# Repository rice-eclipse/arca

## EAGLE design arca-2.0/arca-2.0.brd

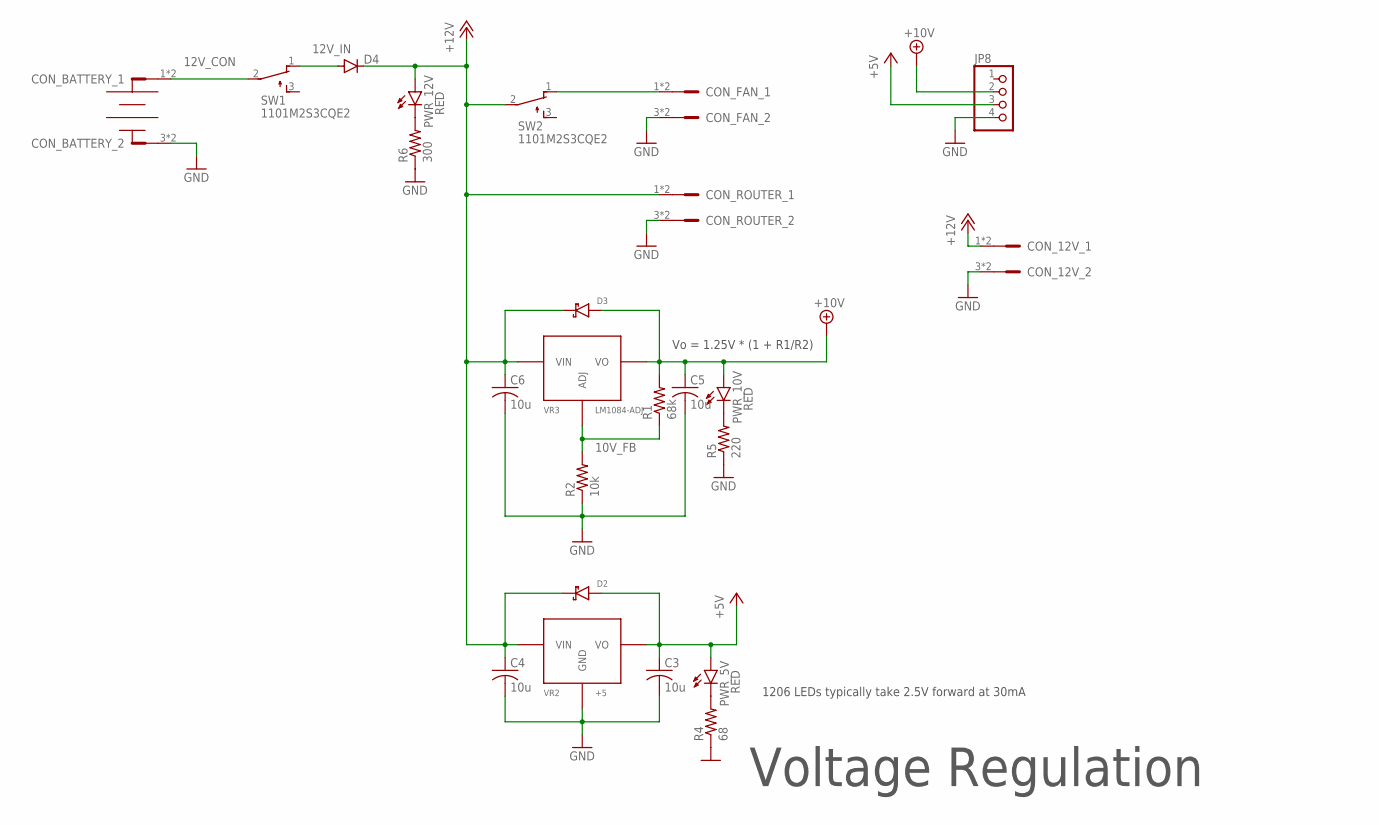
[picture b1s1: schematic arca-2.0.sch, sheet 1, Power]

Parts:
C3, C4, C5, C6: 10u; C1206
CON_12V: LPTA-2POS; 8.2X2
CON_BATTERY: LPTA-2POS; 8.2X2
CON_FAN: LPTA-2POS; 8.2X2
CON_ROUTER: LPTA-2POS; 8.2X2
D2, D3: SS54; SS*
D4: DIODE-DO201-15; DO201-15
JP8: PINHD-1X4; 1X04
PWR_5V, PWR_10V, PWR_12V: RED; CHIPLED_1206
R1: 68k; R1206
R2: 10k; R1206
R4: 68; R1206
R5: 220; R1206
R6: 300; R1206
SW1, SW2: 1101M2S3CQE2
VR2: +5; TO-263-3L
VR3: LM1084-ADJ; TO-263-3L

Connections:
10V_FB: R1.1, R2.2, VR3.P$1 (ADJ)
12V_CON: CON_BATTERY.1, CON_BATTERY.2, SW1.2
12V_IN: D4.A, SW1.1 (O)
+5V: C3.1, D2.P$2, JP8.3, PWR_5V.A, VR2.P$2 (VO), VR2.P$4 (VO), VR2.P$5 (VO); also elsewhere on the board
+10V: C5.1, D3.P$2, JP8.2, PWR_10V.A, R1.2, VR3.P$2 (VO), VR3.P$4 (VO), VR3.P$5 (VO); also elsewhere on the board
+12V: C4.1, C6.1, CON_12V.1, CON_12V.2, CON_ROUTER.1, CON_ROUTER.2, D2.P$1, D3.P$1, D4.C, PWR_12V.A, SW2.2, VR2.P$3 (VIN), VR3.P$3 (VIN); also elsewhere on the board
GND: C3.2, C4.2, C5.2, C6.2, CON_12V.3, CON_12V.4, CON_BATTERY.3, CON_BATTERY.4, CON_FAN.3, CON_FAN.4, CON_ROUTER.3, CON_ROUTER.4, JP8.4, R2.1, R4.1, R5.1, R6.1, VR2.P$1 (GND); also elsewhere on the board
unnamed: PWR_5V.C, R4.2
unnamed: PWR_10V.C, R5.2
unnamed: PWR_12V.C, R6.2
unnamed: CON_FAN.1, CON_FAN.2, SW2.1 (O)

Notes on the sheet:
Vo = 1.25V * (1 + R1/R2)
1206 LEDs typically take 2.5V forward at 30mA
Voltage Regulation

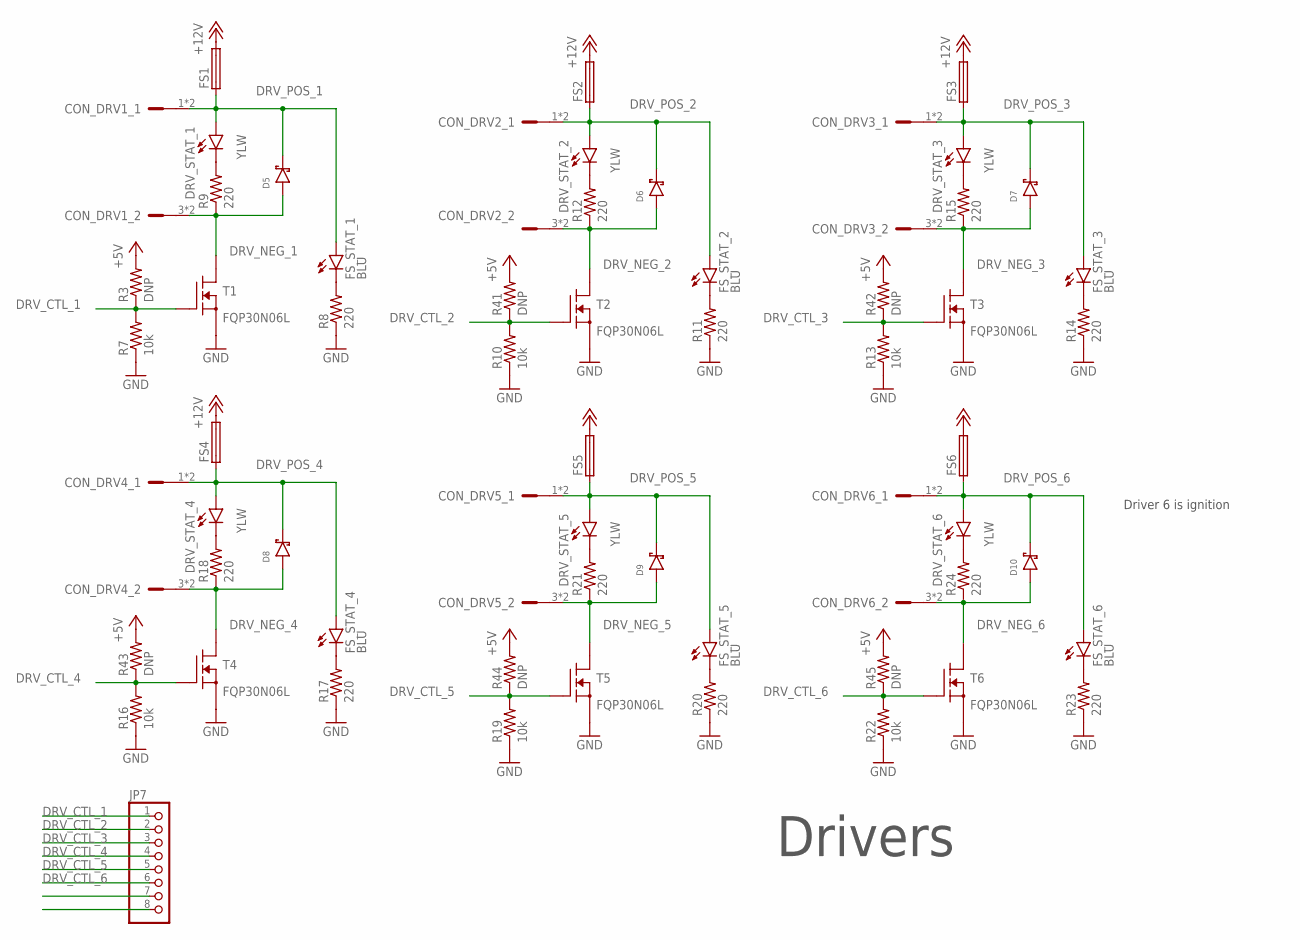
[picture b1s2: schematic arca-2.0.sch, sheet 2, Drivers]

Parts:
CON_DRV1, CON_DRV2, CON_DRV3, CON_DRV4, CON_DRV5, CON_DRV6: LPTA-2POS; 8.2X2
D5, D6, D7, D8, D9, D10: SS54; SS*
DRV_STAT_1, DRV_STAT_2, DRV_STAT_3, DRV_STAT_4, DRV_STAT_5, DRV_STAT_6: YLW; CHIPLED_1206
FS1, FS2, FS3, FS4, FS5, FS6: HOLDER_3588-20; 3588-20
FS_STAT_1, FS_STAT_2, FS_STAT_3, FS_STAT_4, FS_STAT_5, FS_STAT_6: BLU; CHIPLED_1206
JP7: PINHD-1X8; 1X08
R3, R41, R42, R43, R44, R45: DNP; R1206
R7, R10, R13, R16, R19, R22: 10k; R1206
R8, R9, R11, R12, R14, R15, R17, R18, R20, R21, R23, R24: 220; R1206
T1, T2, T3, T4, T5, T6: FQP30N06L; TO220V

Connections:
+5V: R3.2, R41.2, R42.2, R43.2, R44.2, R45.2; also elsewhere on the board
+12V: FS1.P$3 (2), FS1.P$4 (2), FS2.P$3 (2), FS2.P$4 (2), FS3.P$3 (2), FS3.P$4 (2), FS4.P$3 (2), FS4.P$4 (2), FS5.P$3 (2), FS5.P$4 (2), FS6.P$3 (2), FS6.P$4 (2); also elsewhere on the board
DRV_CTL_1: JP7.1, R3.1, R7.2, T1.1 (G); also elsewhere on the board
DRV_CTL_2: JP7.2, R10.2, R41.1, T2.1 (G); also elsewhere on the board
DRV_CTL_3: JP7.3, R13.2, R42.1, T3.1 (G); also elsewhere on the board
DRV_CTL_4: JP7.4, R16.2, R43.1, T4.1 (G); also elsewhere on the board
DRV_CTL_5: JP7.5, R19.2, R44.1, T5.1 (G); also elsewhere on the board
DRV_CTL_6: JP7.6, R22.2, R45.1, T6.1 (G); also elsewhere on the board
DRV_NEG_1: CON_DRV1.3, CON_DRV1.4, D5.P$2, R9.1, T1.2 (D)
DRV_NEG_2: CON_DRV2.3, CON_DRV2.4, D6.P$2, R12.1, T2.2 (D)
DRV_NEG_3: CON_DRV3.3, CON_DRV3.4, D7.P$2, R15.1, T3.2 (D)
DRV_NEG_4: CON_DRV4.3, CON_DRV4.4, D8.P$2, R18.1, T4.2 (D)
DRV_NEG_5: CON_DRV5.3, CON_DRV5.4, D9.P$2, R21.1, T5.2 (D)
DRV_NEG_6: CON_DRV6.3, CON_DRV6.4, D10.P$2, R24.1, T6.2 (D)
DRV_POS_1: CON_DRV1.1, CON_DRV1.2, D5.P$1, DRV_STAT_1.A, FS1.P$1 (1), FS1.P$2 (1), FS_STAT_1.A
DRV_POS_2: CON_DRV2.1, CON_DRV2.2, D6.P$1, DRV_STAT_2.A, FS2.P$1 (1), FS2.P$2 (1), FS_STAT_2.A
DRV_POS_3: CON_DRV3.1, CON_DRV3.2, D7.P$1, DRV_STAT_3.A, FS3.P$1 (1), FS3.P$2 (1), FS_STAT_3.A
DRV_POS_4: CON_DRV4.1, CON_DRV4.2, D8.P$1, DRV_STAT_4.A, FS4.P$1 (1), FS4.P$2 (1), FS_STAT_4.A
DRV_POS_5: CON_DRV5.1, CON_DRV5.2, D9.P$1, DRV_STAT_5.A, FS5.P$1 (1), FS5.P$2 (1), FS_STAT_5.A
DRV_POS_6: CON_DRV6.1, CON_DRV6.2, D10.P$1, DRV_STAT_6.A, FS6.P$1 (1), FS6.P$2 (1), FS_STAT_6.A
GND: R7.1, R8.1, R10.1, R11.1, R13.1, R14.1, R16.1, R17.1, R19.1, R20.1, R22.1, R23.1, T1.3 (S), T2.3 (S), T3.3 (S), T4.3 (S), T5.3 (S), T6.3 (S); also elsewhere on the board
unnamed: FS_STAT_2.C, R11.2
unnamed: DRV_STAT_2.C, R12.2
unnamed: FS_STAT_3.C, R14.2
unnamed: FS_STAT_1.C, R8.2
unnamed: DRV_STAT_1.C, R9.2
unnamed: DRV_STAT_3.C, R15.2
unnamed: FS_STAT_4.C, R17.2
unnamed: DRV_STAT_4.C, R18.2
unnamed: FS_STAT_5.C, R20.2
unnamed: DRV_STAT_5.C, R21.2
unnamed: FS_STAT_6.C, R23.2
unnamed: DRV_STAT_6.C, R24.2

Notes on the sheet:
Driver 6 is ignition
Drivers

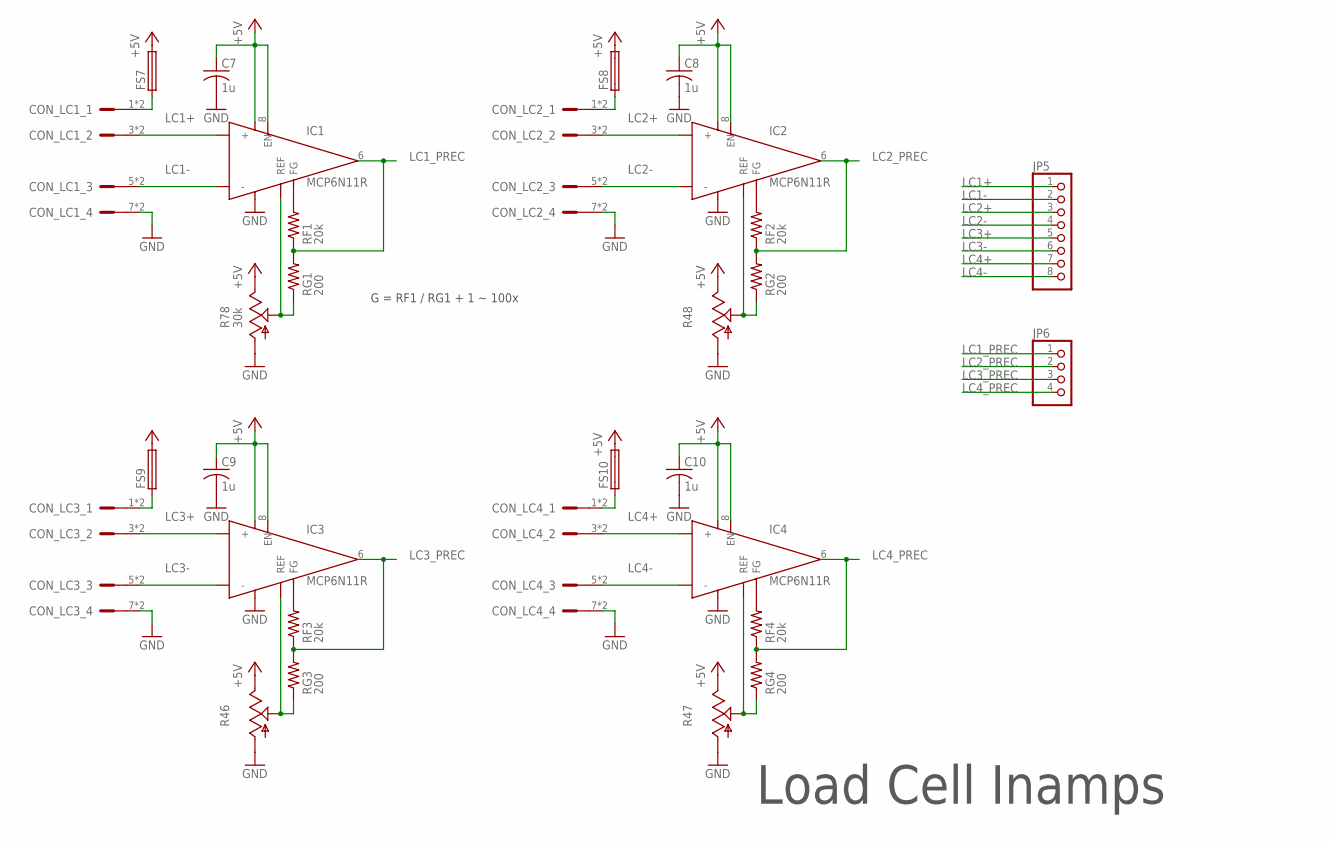
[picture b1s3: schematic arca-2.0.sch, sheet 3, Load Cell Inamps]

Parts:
C7, C8, C9, C10: 1u; C1206
CON_LC1, CON_LC2, CON_LC3, CON_LC4: LPTA-4POS; 8.2X4
FS7, FS8, FS9, FS10: HOLDER_3588-20; 3588-20
IC1, IC2, IC3, IC4: MCP6N11R; SO-8
JP5: PINHD-1X8; 1X08
JP6: PINHD-1X4; 1X04
R46, R47, R48: TRIM_US-S64W; S64W
R78: 30k; S64W
RF1, RF2, RF3, RF4: 20k; R1206
RG1, RG2, RG3, RG4: 200; R1206

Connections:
+5V: C7.1, C8.1, C9.1, C10.1, FS7.P$3 (2), FS7.P$4 (2), FS8.P$3 (2), FS8.P$4 (2), FS9.P$3 (2), FS9.P$4 (2), FS10.P$3 (2), FS10.P$4 (2), IC1.7 (+V), IC1.8 (EN), IC2.7 (+V), IC2.8 (EN), IC3.7 (+V), IC3.8 (EN), IC4.7 (+V), IC4.8 (EN), R46.E, R47.E, R48.E, R78.E; also elsewhere on the board
GND: C7.2, C8.2, C9.2, C10.2, CON_LC1.7, CON_LC1.8, CON_LC2.7, CON_LC2.8, CON_LC3.7, CON_LC3.8, CON_LC4.7, CON_LC4.8, IC1.4 (-V), IC2.4 (-V), IC3.4 (-V), IC4.4 (-V), R46.A, R47.A, R48.A, R78.A; also elsewhere on the board
LC1+: CON_LC1.3, CON_LC1.4, IC1.3 (+), JP5.1
LC1-: CON_LC1.5, CON_LC1.6, IC1.2 (-), JP5.2
LC1_PREC: IC1.6 (OUT), JP6.1, RF1.1, RG1.2; also elsewhere on the board
LC2+: CON_LC2.3, CON_LC2.4, IC2.3 (+), JP5.3
LC2-: CON_LC2.5, CON_LC2.6, IC2.2 (-), JP5.4
LC2_PREC: IC2.6 (OUT), JP6.2, RF2.1, RG2.2; also elsewhere on the board
LC3+: CON_LC3.3, CON_LC3.4, IC3.3 (+), JP5.5
LC3-: CON_LC3.5, CON_LC3.6, IC3.2 (-), JP5.6
LC3_PREC: IC3.6 (OUT), JP6.3, RF3.1, RG3.2; also elsewhere on the board
LC4+: CON_LC4.3, CON_LC4.4, IC4.3 (+), JP5.7
LC4-: CON_LC4.5, CON_LC4.6, IC4.2 (-), JP5.8
LC4_PREC: IC4.6 (OUT), JP6.4, RF4.1, RG4.2; also elsewhere on the board
unnamed: IC1.5 (REF), R78.S, RG1.1
unnamed: IC2.5 (REF), R48.S, RG2.1
unnamed: IC1.1 (FG), RF1.2
unnamed: IC2.1 (FG), RF2.2
unnamed: IC3.1 (FG), RF3.2
unnamed: IC4.1 (FG), RF4.2
unnamed: IC4.5 (REF), R47.S, RG4.1
unnamed: IC3.5 (REF), R46.S, RG3.1
unnamed: CON_LC1.1, CON_LC1.2, FS7.P$1 (1), FS7.P$2 (1)
unnamed: CON_LC2.1, CON_LC2.2, FS8.P$1 (1), FS8.P$2 (1)
unnamed: CON_LC3.1, CON_LC3.2, FS9.P$1 (1), FS9.P$2 (1)
unnamed: CON_LC4.1, CON_LC4.2, FS10.P$1 (1), FS10.P$2 (1)

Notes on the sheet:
Load Cell Inamps
G = RF1 / RG1 + 1 ~ 100x

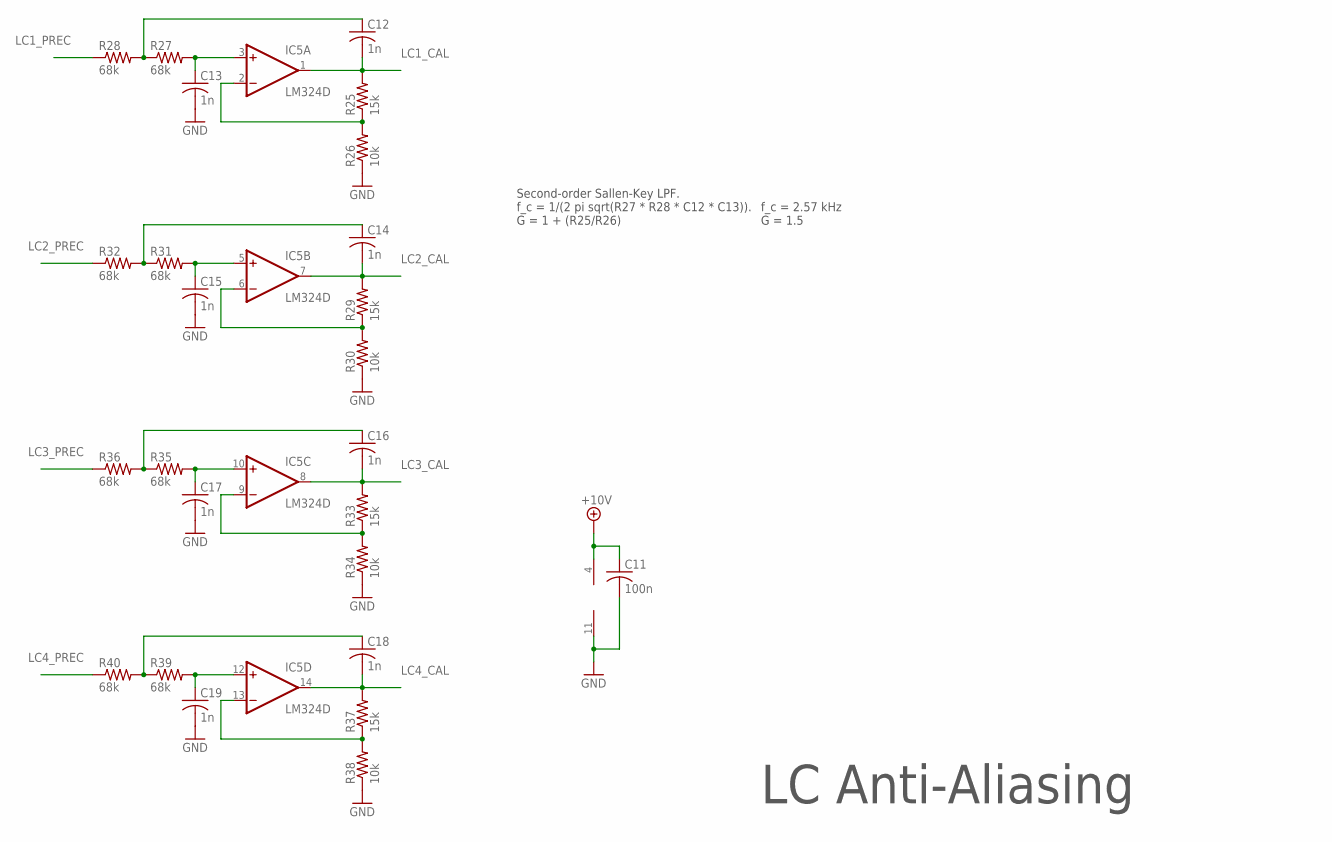
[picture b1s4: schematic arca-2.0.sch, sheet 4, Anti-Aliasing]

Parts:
C11: 100n; C1206
C12, C13, C14, C15, C16, C17, C18, C19: 1n; C1206
IC5: LM324D; SO14
R25, R29, R33, R37: 15k; R1206
R26, R30, R34, R38: 10k; R1206
R27, R28, R31, R32, R35, R36, R39, R40: 68k; R1206

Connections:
+10V: C11.1, IC5.4 (V+); also elsewhere on the board
GND: C11.2, C13.2, C15.2, C17.2, C19.2, IC5.11 (V-), R26.1, R30.1, R34.1, R38.1; also elsewhere on the board
LC1_CAL: C12.2, IC5.1 (OUT), R25.2; also elsewhere on the board
LC1_PREC: R28.1; also elsewhere on the board
LC2_CAL: C14.2, IC5.7 (OUT), R29.2; also elsewhere on the board
LC2_PREC: R32.1; also elsewhere on the board
LC3_CAL: C16.2, IC5.8 (OUT), R33.2; also elsewhere on the board
LC3_PREC: R36.1; also elsewhere on the board
LC4_CAL: C18.2, IC5.14 (OUT), R37.2; also elsewhere on the board
LC4_PREC: R40.1; also elsewhere on the board
unnamed: IC5.9 (-IN), R33.1, R34.2
unnamed: C17.1, IC5.10 (+IN), R35.2
unnamed: C16.1, R35.1, R36.2
unnamed: IC5.13 (-IN), R37.1, R38.2
unnamed: IC5.2 (-IN), R25.1, R26.2
unnamed: IC5.6 (-IN), R29.1, R30.2
unnamed: C13.1, IC5.3 (+IN), R27.2
unnamed: C12.1, R27.1, R28.2
unnamed: C15.1, IC5.5 (+IN), R31.2
unnamed: C14.1, R31.1, R32.2
unnamed: C19.1, IC5.12 (+IN), R39.2
unnamed: C18.1, R39.1, R40.2

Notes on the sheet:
Second-order Sallen-Key LPF. f_c = 1/(2 pi sqrt(R27 * R28 * C12 * C13)). G = 1 + (R25/R26)
f_c = 2.57 kHz G = 1.5
LC Anti-Aliasing

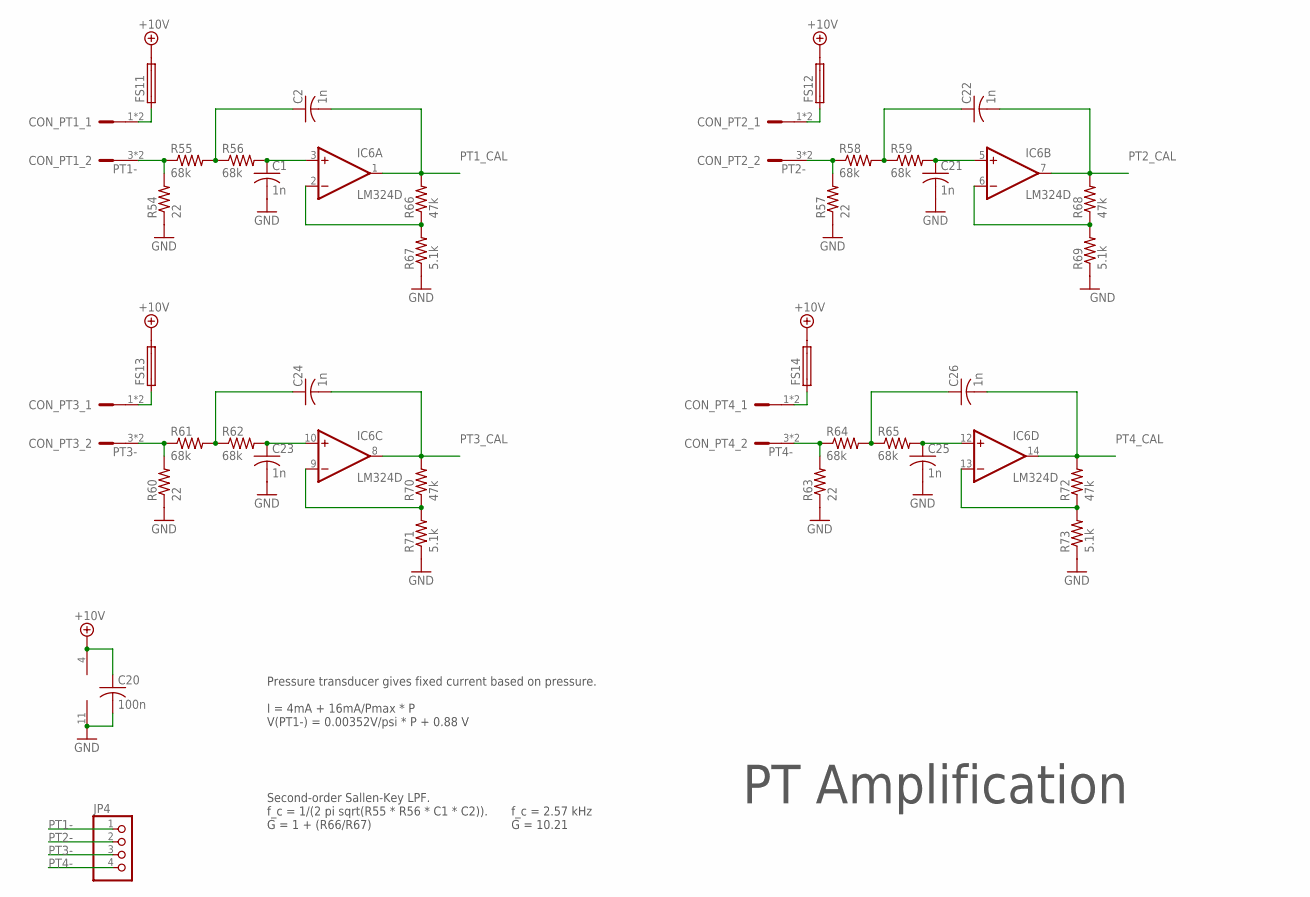
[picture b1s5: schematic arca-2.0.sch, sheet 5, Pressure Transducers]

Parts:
C1, C2, C21, C22, C23, C24, C25, C26: 1n; C1206
C20: 100n; C1206
CON_PT1, CON_PT2, CON_PT3, CON_PT4: LPTA-2POS; 8.2X2
FS11, FS12, FS13, FS14: HOLDER_3588-20; 3588-20
IC6: LM324D; SO14
JP4: PINHD-1X4; 1X04
R54, R57, R60, R63: 22; R1206
R55, R56, R58, R59, R61, R62, R64, R65: 68k; R1206
R66, R68, R70, R72: 47k; R1206
R67, R69, R71, R73: 5.1k; R1206

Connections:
+10V: C20.1, FS11.P$3 (2), FS11.P$4 (2), FS12.P$3 (2), FS12.P$4 (2), FS13.P$3 (2), FS13.P$4 (2), FS14.P$3 (2), FS14.P$4 (2), IC6.4 (V+); also elsewhere on the board
GND: C1.2, C20.2, C21.2, C23.2, C25.2, IC6.11 (V-), R54.1, R57.1, R60.1, R63.1, R67.1, R69.1, R71.1, R73.1; also elsewhere on the board
unnamed: C22.1, R58.2, R59.1
unnamed: C2.1, R55.2, R56.1
unnamed: C1.1, IC6.3 (+IN), R56.2
unnamed: C21.1, IC6.5 (+IN), R59.2
unnamed: C24.1, R61.2, R62.1
unnamed: C23.1, IC6.10 (+IN), R62.2
unnamed: C26.1, R64.2, R65.1
unnamed: C25.1, IC6.12 (+IN), R65.2
unnamed: IC6.13 (-IN), R72.1, R73.2
unnamed: IC6.9 (-IN), R70.1, R71.2
unnamed: IC6.6 (-IN), R68.1, R69.2
unnamed: IC6.2 (-IN), R66.1, R67.2
unnamed: CON_PT1.1, CON_PT1.2, FS11.P$1 (1), FS11.P$2 (1)
unnamed: CON_PT2.1, CON_PT2.2, FS12.P$1 (1), FS12.P$2 (1)
unnamed: CON_PT3.1, CON_PT3.2, FS13.P$1 (1), FS13.P$2 (1)
unnamed: CON_PT4.1, CON_PT4.2, FS14.P$1 (1), FS14.P$2 (1)
PT1-: CON_PT1.3, CON_PT1.4, JP4.1, R54.2, R55.1
PT1_CAL: C2.2, IC6.1 (OUT), R66.2; also elsewhere on the board
PT2-: CON_PT2.3, CON_PT2.4, JP4.2, R57.2, R58.1
PT2_CAL: C22.2, IC6.7 (OUT), R68.2; also elsewhere on the board
PT3-: CON_PT3.3, CON_PT3.4, JP4.3, R60.2, R61.1
PT3_CAL: C24.2, IC6.8 (OUT), R70.2; also elsewhere on the board
PT4-: CON_PT4.3, CON_PT4.4, JP4.4, R63.2, R64.1
PT4_CAL: C26.2, IC6.14 (OUT), R72.2; also elsewhere on the board

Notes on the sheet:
Pressure transducer gives fixed current based on pressure. I = 4mA + 16mA/Pmax * P V(PT1-) = 0.00352V/psi * P + 0.88 V
Second-order Sallen-Key LPF. f_c = 1/(2 pi sqrt(R55 * R56 * C1 * C2)). G = 1 + (R66/R67)
f_c = 2.57 kHz G = 10.21
PT Amplification

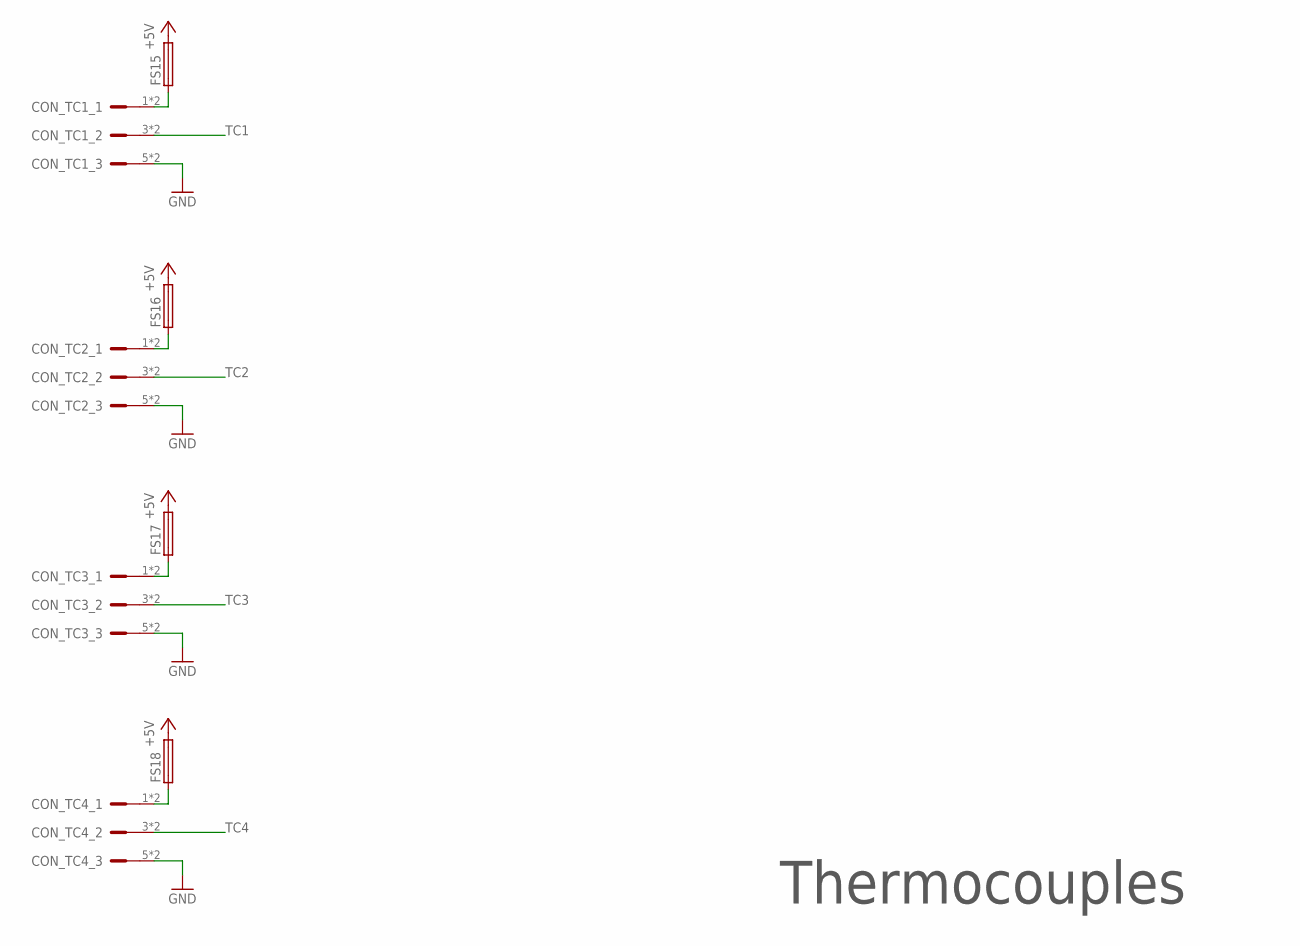
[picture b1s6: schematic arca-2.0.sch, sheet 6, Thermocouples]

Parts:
CON_TC1, CON_TC2, CON_TC3, CON_TC4: LPTA-3POS; 8.2X3
FS15, FS16, FS17, FS18: HOLDER_3588-20; 3588-20

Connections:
+5V: FS15.P$3 (2), FS15.P$4 (2), FS16.P$3 (2), FS16.P$4 (2), FS17.P$3 (2), FS17.P$4 (2), FS18.P$3 (2), FS18.P$4 (2); also elsewhere on the board
GND: CON_TC1.5, CON_TC1.6, CON_TC2.5, CON_TC2.6, CON_TC3.5, CON_TC3.6, CON_TC4.5, CON_TC4.6; also elsewhere on the board
unnamed: CON_TC1.1, CON_TC1.2, FS15.P$1 (1), FS15.P$2 (1)
unnamed: CON_TC2.1, CON_TC2.2, FS16.P$1 (1), FS16.P$2 (1)
unnamed: CON_TC3.1, CON_TC3.2, FS17.P$1 (1), FS17.P$2 (1)
unnamed: CON_TC4.1, CON_TC4.2, FS18.P$1 (1), FS18.P$2 (1)
TC1: CON_TC1.3, CON_TC1.4; also elsewhere on the board
TC2: CON_TC2.3, CON_TC2.4; also elsewhere on the board
TC3: CON_TC3.3, CON_TC3.4; also elsewhere on the board
TC4: CON_TC4.3, CON_TC4.4; also elsewhere on the board

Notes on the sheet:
Thermocouples

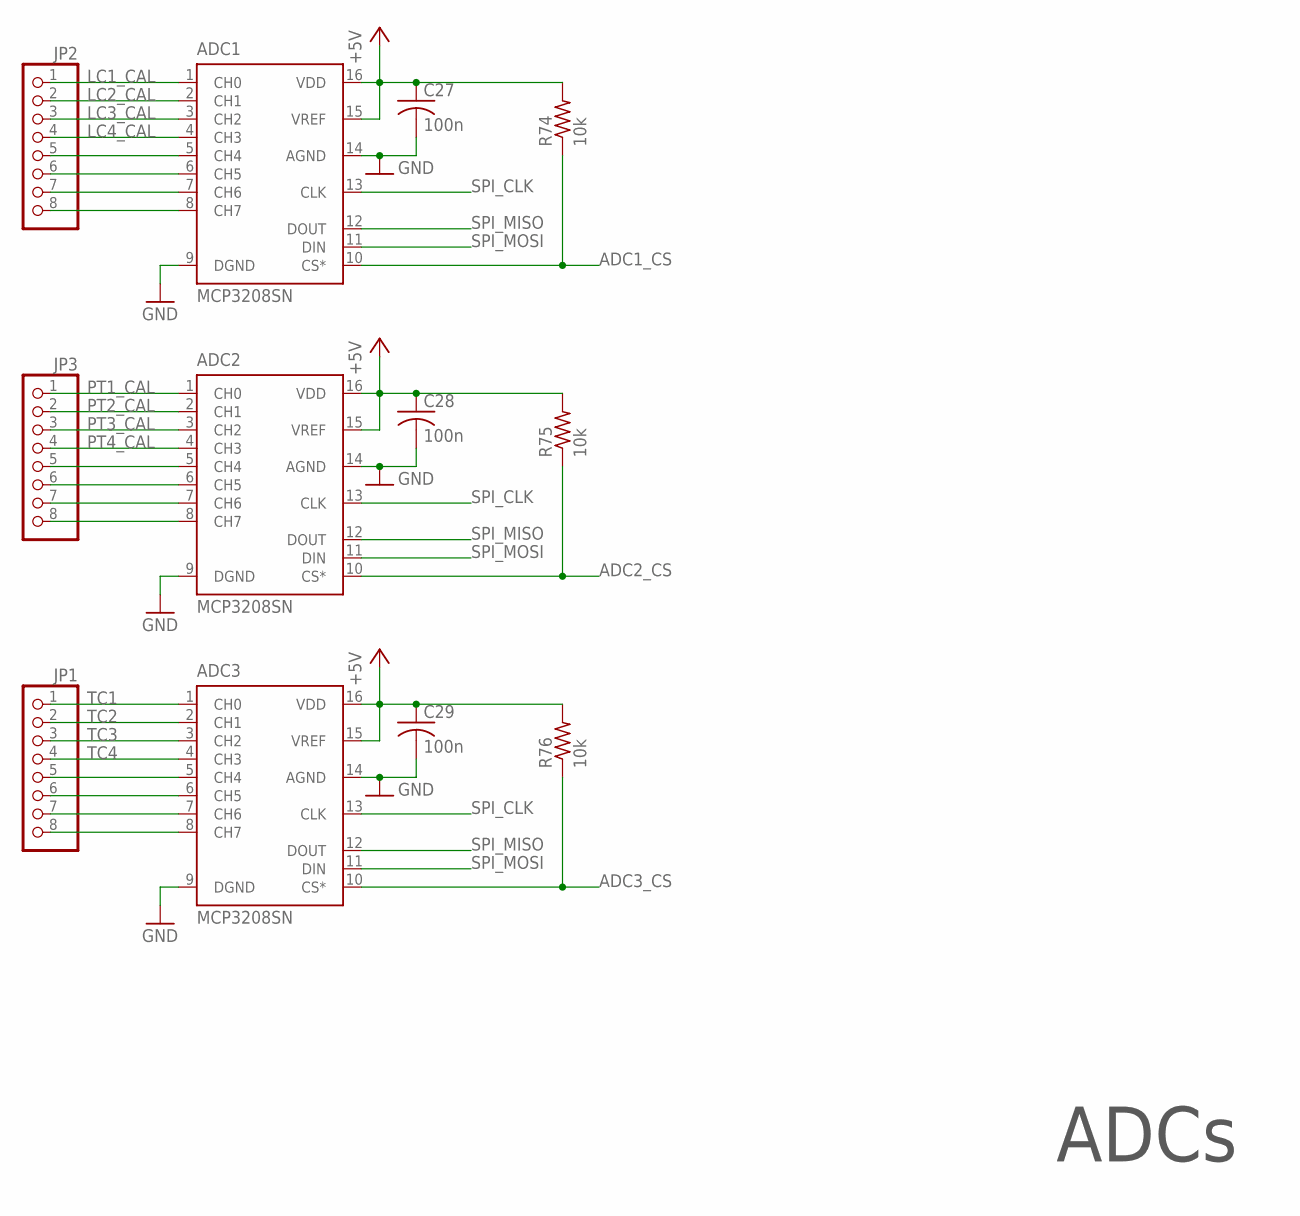
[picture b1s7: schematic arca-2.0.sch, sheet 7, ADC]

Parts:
ADC1, ADC2, ADC3: MCP3208SN; SO-16
C27, C28, C29: 100n; C1206
JP1, JP2, JP3: PINHD-1X8; 1X08
R74, R75, R76: 10k; R1206

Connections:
+5V: ADC1.15 (VREF), ADC1.16 (VDD), ADC2.15 (VREF), ADC2.16 (VDD), ADC3.15 (VREF), ADC3.16 (VDD), C27.1, C28.1, C29.1, R74.2, R75.2, R76.2; also elsewhere on the board
ADC1_CS: ADC1.10 (CS*), R74.1; also elsewhere on the board
ADC2_CS: ADC2.10 (CS*), R75.1; also elsewhere on the board
ADC3_CS: ADC3.10 (CS*), R76.1; also elsewhere on the board
GND: ADC1.9 (DGND), ADC1.14 (AGND), ADC2.9 (DGND), ADC2.14 (AGND), ADC3.9 (DGND), ADC3.14 (AGND), C27.2, C28.2, C29.2; also elsewhere on the board
LC1_CAL: ADC1.1 (CH0), JP2.1; also elsewhere on the board
LC2_CAL: ADC1.2 (CH1), JP2.2; also elsewhere on the board
LC3_CAL: ADC1.3 (CH2), JP2.3; also elsewhere on the board
LC4_CAL: ADC1.4 (CH3), JP2.4; also elsewhere on the board
unnamed: ADC3.5 (CH4), JP1.5
unnamed: ADC3.6 (CH5), JP1.6
unnamed: ADC3.7 (CH6), JP1.7
unnamed: ADC3.8 (CH7), JP1.8
unnamed: ADC1.8 (CH7), JP2.8
unnamed: ADC1.7 (CH6), JP2.7
unnamed: ADC1.6 (CH5), JP2.6
unnamed: ADC1.5 (CH4), JP2.5
unnamed: ADC2.5 (CH4), JP3.5
unnamed: ADC2.6 (CH5), JP3.6
unnamed: ADC2.7 (CH6), JP3.7
unnamed: ADC2.8 (CH7), JP3.8
PT1_CAL: ADC2.1 (CH0), JP3.1; also elsewhere on the board
PT2_CAL: ADC2.2 (CH1), JP3.2; also elsewhere on the board
PT3_CAL: ADC2.3 (CH2), JP3.3; also elsewhere on the board
PT4_CAL: ADC2.4 (CH3), JP3.4; also elsewhere on the board
SPI_CLK: ADC1.13 (CLK), ADC2.13 (CLK), ADC3.13 (CLK); also elsewhere on the board
SPI_MISO: ADC1.12 (DOUT), ADC2.12 (DOUT), ADC3.12 (DOUT); also elsewhere on the board
SPI_MOSI: ADC1.11 (DIN), ADC2.11 (DIN), ADC3.11 (DIN); also elsewhere on the board
TC1: ADC3.1 (CH0), JP1.1; also elsewhere on the board
TC2: ADC3.2 (CH1), JP1.2; also elsewhere on the board
TC3: ADC3.3 (CH2), JP1.3; also elsewhere on the board
TC4: ADC3.4 (CH3), JP1.4; also elsewhere on the board

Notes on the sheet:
ADCs

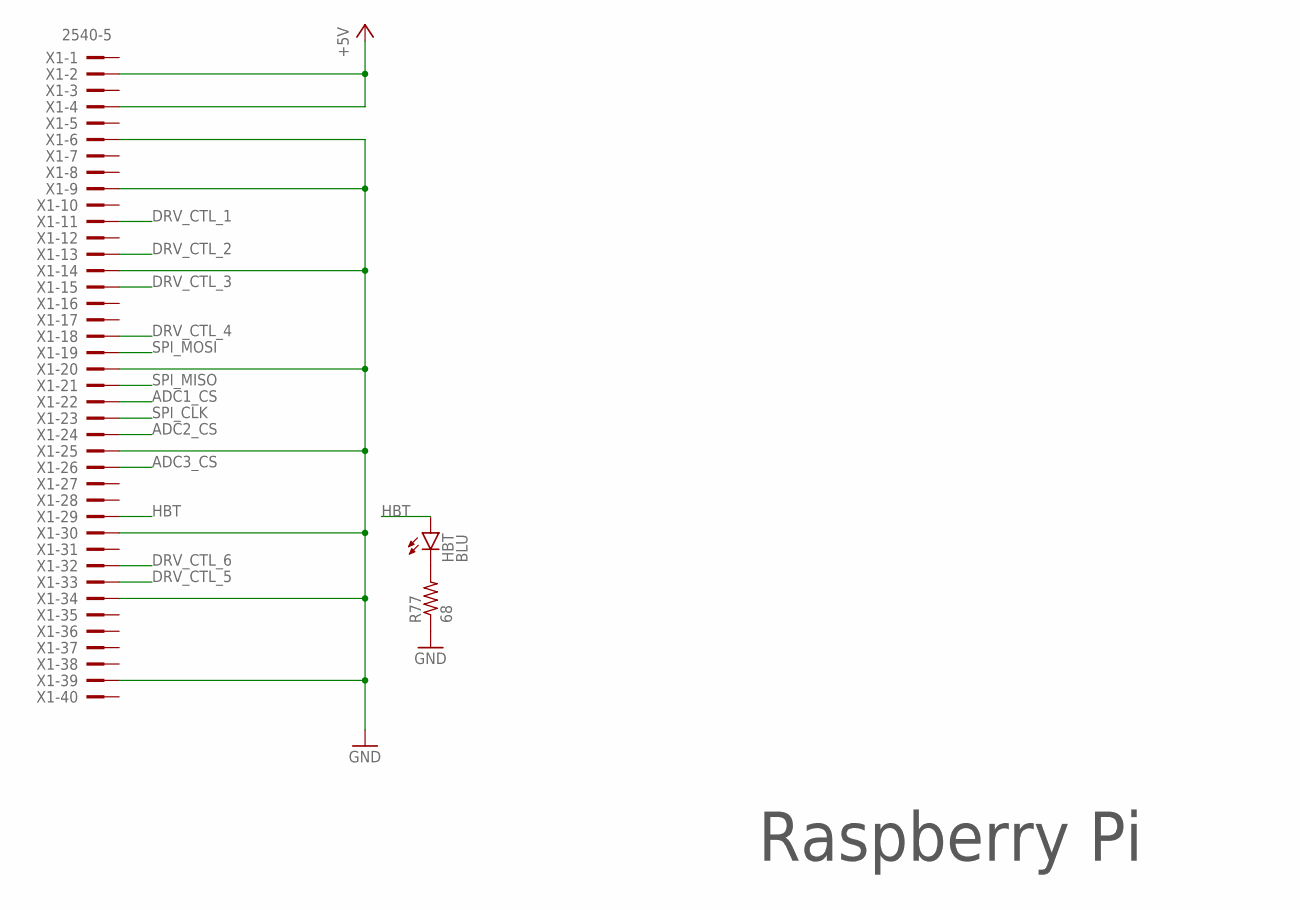
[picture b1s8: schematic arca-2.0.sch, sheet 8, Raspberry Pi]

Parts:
HBT: BLU; CHIPLED_1206
R77: 68; R1206
X1: 2540-5; PAK100/2500-5-40

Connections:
+5V: X1.2, X1.4; also elsewhere on the board
ADC1_CS: X1.22; also elsewhere on the board
ADC2_CS: X1.24; also elsewhere on the board
ADC3_CS: X1.26; also elsewhere on the board
DRV_CTL_1: X1.11; also elsewhere on the board
DRV_CTL_2: X1.13; also elsewhere on the board
DRV_CTL_3: X1.15; also elsewhere on the board
DRV_CTL_4: X1.18; also elsewhere on the board
DRV_CTL_5: X1.33; also elsewhere on the board
DRV_CTL_6: X1.32; also elsewhere on the board
GND: R77.1, X1.6, X1.9, X1.14, X1.20, X1.25, X1.30, X1.34, X1.39; also elsewhere on the board
HBT: HBT.A, X1.29
unnamed: HBT.C, R77.2
SPI_CLK: X1.23; also elsewhere on the board
SPI_MISO: X1.21; also elsewhere on the board
SPI_MOSI: X1.19; also elsewhere on the board

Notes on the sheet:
Raspberry Pi

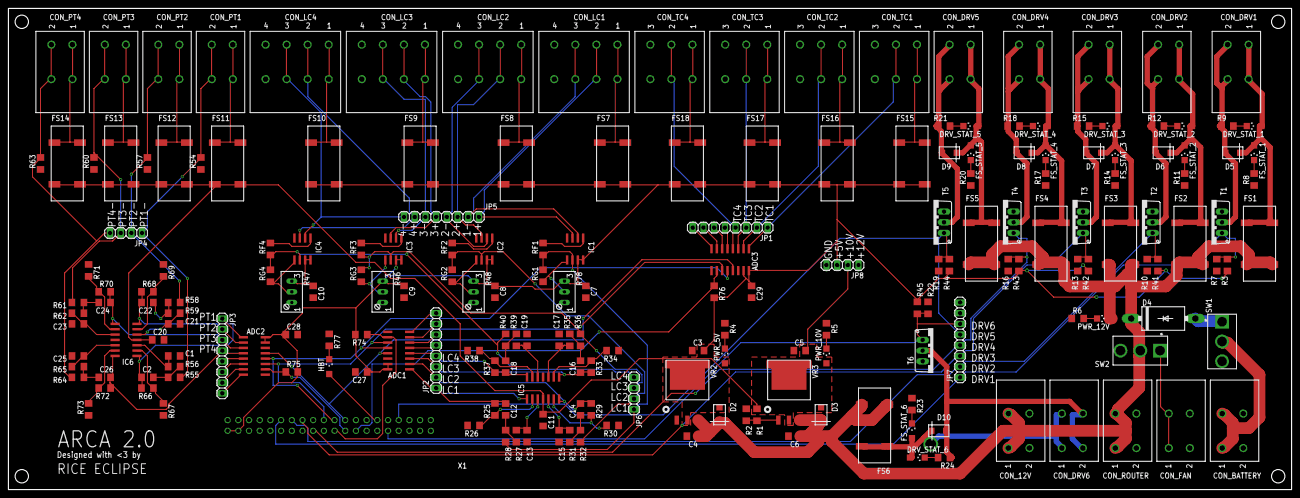
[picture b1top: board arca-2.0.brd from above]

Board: 2 copper layers, 304.8 x 114.3 mm, 203 parts (1 on the bottom side), 133 nets.

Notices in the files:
parts and their libraries:
COPYRIGHT: Copyright (C) 2015 Accelerated Designs. All rights reserved
